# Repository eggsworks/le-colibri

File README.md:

# le colibri

Le Colibri is a 30-key unibody split keyboard inspired by Le Chiffre and the Hummingbird.

## Disclaimers

1. This keyboard came to me in a dream so I had to bring it into the waking world. It is not necessarily good. But here it is.
2. The alternate layout in this branch has not yet been tested!

## FAQ

**Why not just [chiffchaff](https://github.com/kilipan/chiffchaff)?**  
Like I said, this keyboard was designed in a dream. The dreamt keyboard was not chiffchaff but something much worse, which you see here.

**Can I use a regular Chiffre case or PCB?**  
No, it is basically completely incompatible. See *Case* section below.

## BOM

- 30x SOD-123 1N4148 diodes
- 30x Kailh MX hotswap sockets
- One Seeduino XIAO (designed for RP2040, but will work with others -- maybe you can even make it wireless if you bodge a battery onto the NRF one!**

## Case

The switchplates are obviously incompatible with a normal Chiffre. The in-plane XIAO makes this keyboard incompatible with the bottom case. And the reduced number of keys would make it dumb to use the top, unless you like huge gaps. Custom case files can be found in [case/](case/).

Screw the switchplate into the case before putting any switches in it - the PCB blocks a couple of the holes.

The only support needed during printing is on the bottom case, near the outer edges of the screw holes.

Also be aware that the switchplate does not currently have cutouts for stabilizers (though the PCB does have stabilizer support).

## Firmware

Firmware is available in the [eggsworks zmk-config repo](https://github.com/eggsworks/zmk-config/).

## Assembly

1. Solder the Xiao, with components facing the back side of the board, as pictured here. The intend of mid-mounting the Xiao is to put the USB port at the same height as it is on a normal Le Chiffre PCB, so try to get it lined up such that the top of the Xiao PCB lines up with the bottom of the Le Colibri PCB.
2. Solder the diodes.
3. Solder the sockets.
4. Mount the switchplates to the top case using self-tapping M2 screws.
5. Insert switches in the sockets to secure the PCB to the case.
6. Flash firmware before closing up the bottom case.
7. Add the bottom case to the assembly and secure it with self-tapping M3 screws.

## Acknowledgements

- Inspired by the original [tominabox1/Le-Chiffre-Keyboard](https://github.com/tominabox1/Le-Chiffre-Keyboard/) and [PJE66/hummingbird](https://github.com/PJE66/hummingbird)
- MCU footprint derived from [ebastler/marbastlib](https://github.com/ebastler/marbastlib/)
- Layout derived from ergogen source supplied for [sporkus/le_capybara_keyboard](https://github.com/sporkus/le_capybara_keyboard)
- Logo by Sune
- Case modification by Donny
- Chiffchaff-like alternate layout by ThePurox

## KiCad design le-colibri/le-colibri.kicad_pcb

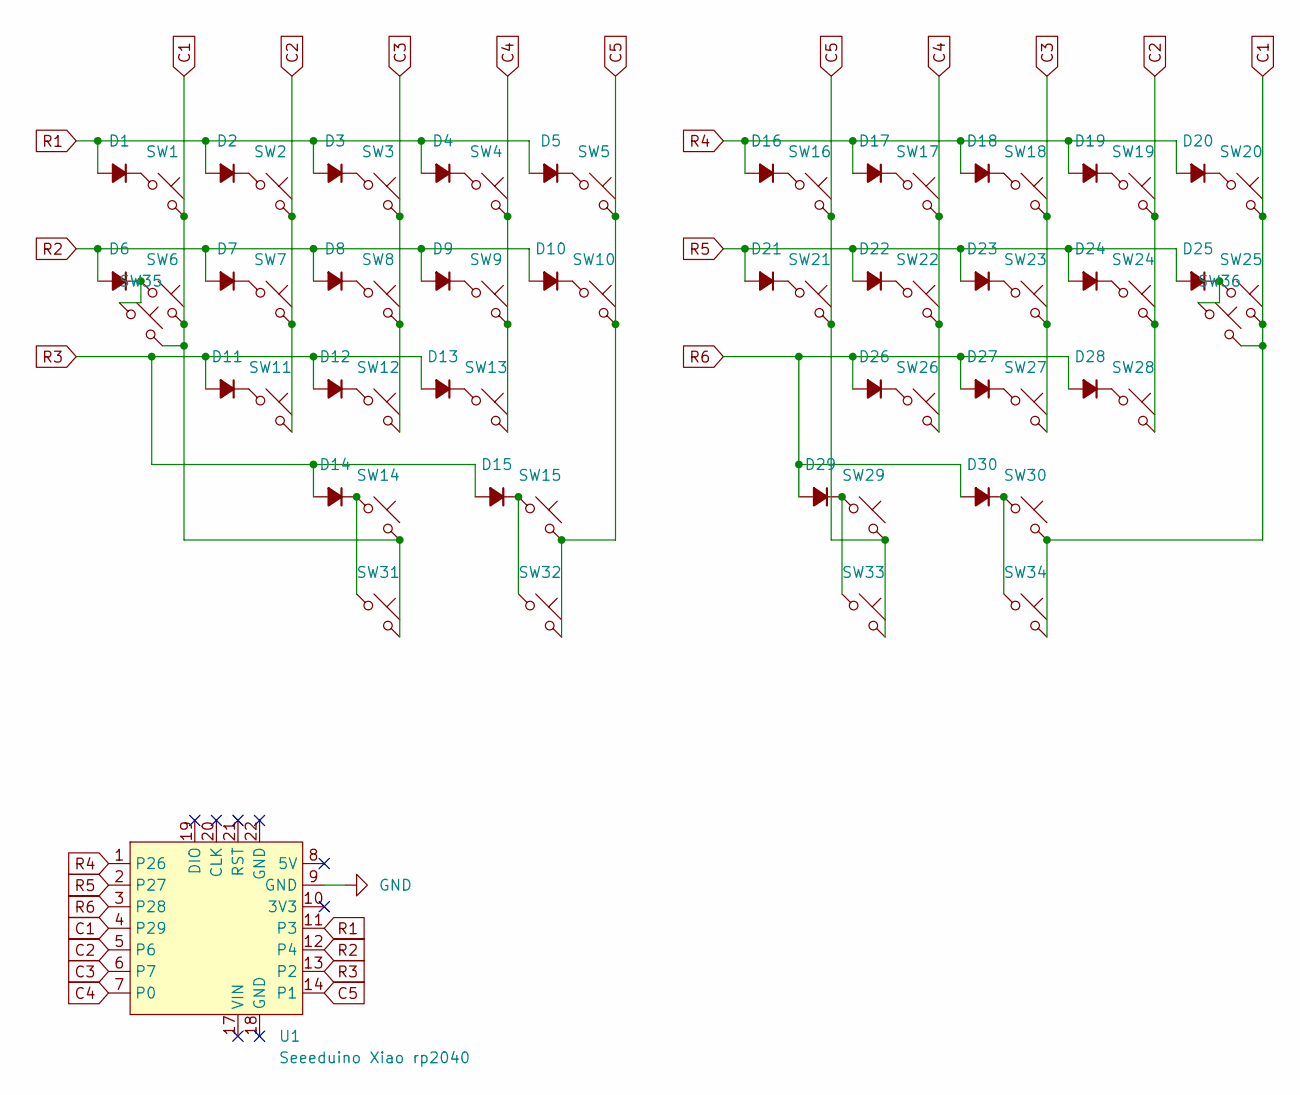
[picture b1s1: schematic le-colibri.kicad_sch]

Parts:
D1, D2, D3, D4, D5, D6, D7, D8, D9, D10, D11, D12, D13, D14, D15, D16, D17, D18, D19, D20, D21, D22, D23, D24, D25, D26, D27, D28, D29, D30: 1N4148; D_SOD-123
SW1, SW2, SW3, SW4, SW5, SW6, SW7, SW8, SW9, SW10, SW11, SW12, SW13, SW14, SW15, SW16, SW17, SW18, SW19, SW20, SW21, SW22, SW23, SW24, SW25, SW26, SW27, SW28, SW29, SW30, SW31, SW32, SW33, SW34, SW35, SW36: CPG151101S11; SW_MX_HS_CPG151101S11_1u
U1: Seeeduino Xiao rp2040; Xiao_rp2040_ACH

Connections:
C1: SW1.2, SW6.2, SW14.2, SW20.2, SW25.2, SW30.2, SW31.2, SW34.2, SW35.2, SW36.2, U1.4 (P29)
C2: SW2.2, SW7.2, SW11.2, SW19.2, SW24.2, SW28.2, U1.5 (P6)
C3: SW3.2, SW8.2, SW12.2, SW18.2, SW23.2, SW27.2, U1.6 (P7)
C4: SW4.2, SW9.2, SW13.2, SW17.2, SW22.2, SW26.2, U1.7 (P0)
C5: SW5.2, SW10.2, SW15.2, SW16.2, SW21.2, SW29.2, SW32.2, SW33.2, U1.14 (P1)
GND: U1.9 (GND)
unnamed: D1.1 (K), SW1.1
unnamed: D2.1 (K), SW2.1
unnamed: D3.1 (K), SW3.1
unnamed: D4.1 (K), SW4.1
unnamed: D5.1 (K), SW5.1
unnamed: D6.1 (K), SW6.1, SW35.1
unnamed: D7.1 (K), SW7.1
unnamed: D8.1 (K), SW8.1
unnamed: D9.1 (K), SW9.1
unnamed: D10.1 (K), SW10.1
unnamed: D11.1 (K), SW11.1
unnamed: D12.1 (K), SW12.1
unnamed: D13.1 (K), SW13.1
unnamed: D14.1 (K), SW14.1, SW31.1
unnamed: D15.1 (K), SW15.1, SW32.1
unnamed: D16.1 (K), SW16.1
unnamed: D17.1 (K), SW17.1
unnamed: D18.1 (K), SW18.1
unnamed: D19.1 (K), SW19.1
unnamed: D20.1 (K), SW20.1
unnamed: D21.1 (K), SW21.1
unnamed: D22.1 (K), SW22.1
unnamed: D23.1 (K), SW23.1
unnamed: D24.1 (K), SW24.1
unnamed: D25.1 (K), SW25.1, SW36.1
unnamed: D26.1 (K), SW26.1
unnamed: D27.1 (K), SW27.1
unnamed: D28.1 (K), SW28.1
unnamed: D29.1 (K), SW29.1, SW33.1
unnamed: D30.1 (K), SW30.1, SW34.1
R1: D1.2 (A), D2.2 (A), D3.2 (A), D4.2 (A), D5.2 (A), U1.11 (P3)
R2: D6.2 (A), D7.2 (A), D8.2 (A), D9.2 (A), D10.2 (A), U1.12 (P4)
R3: D11.2 (A), D12.2 (A), D13.2 (A), D14.2 (A), D15.2 (A), U1.13 (P2)
R4: D16.2 (A), D17.2 (A), D18.2 (A), D19.2 (A), D20.2 (A), U1.1 (P26)
R5: D21.2 (A), D22.2 (A), D23.2 (A), D24.2 (A), D25.2 (A), U1.2 (P27)
R6: D26.2 (A), D27.2 (A), D28.2 (A), D29.2 (A), D30.2 (A), U1.3 (P28)

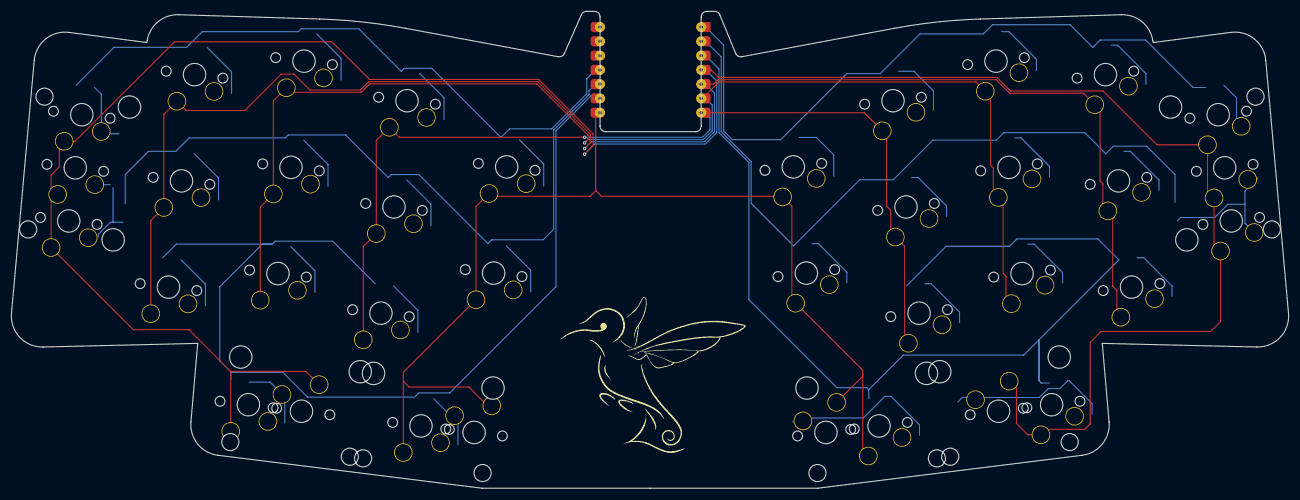
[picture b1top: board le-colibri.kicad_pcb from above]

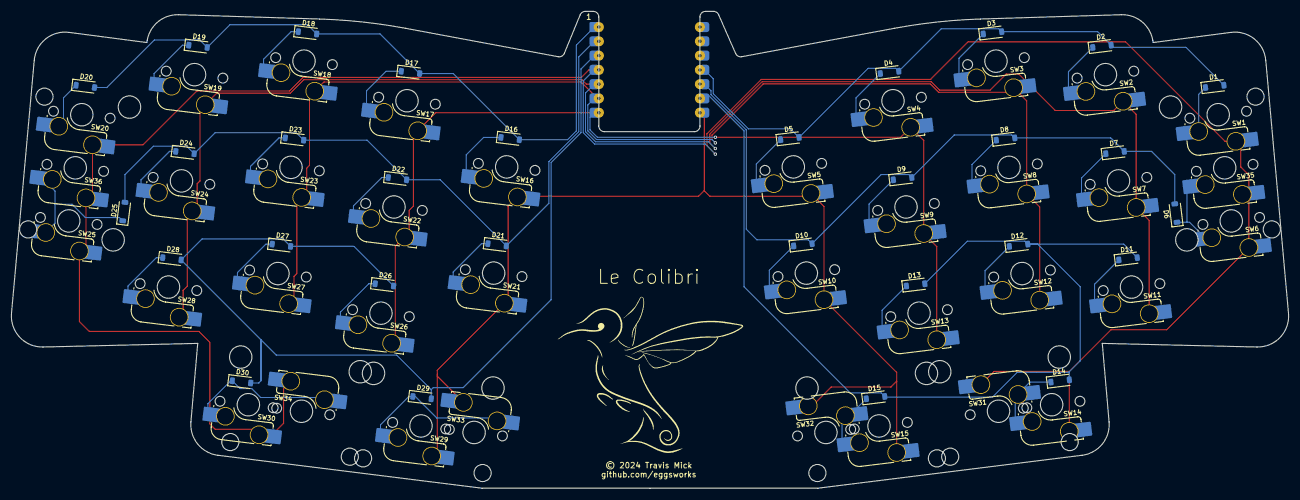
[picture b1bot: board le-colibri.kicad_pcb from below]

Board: 2 copper layers, 227.4 x 84.9 mm, 67 parts (67 on the bottom side), 41 nets.

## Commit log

2024-11-30 fix mirror ref point
2024-12-01 "first" "release"
2024-12-29 update readme etc
2024-12-29 added new options for thumbs and pinkie
2025-01-01 Fixups and switchplates for alt layout

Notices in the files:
le-colibri/le-colibri.kicad_pcb:
© 2024 Travis Mick
